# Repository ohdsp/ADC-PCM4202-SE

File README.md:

# [Open Hardware DSP Platform](http://www.ohdsp.org)
## PCM4202 ADC with single ended inputs
### Revision 1.1
###### ADC-PCM4202-SE (KiCad 4.0.2-stable)
---
# README
### Disclaimer
Copyright Paul Janicki 2016

Licensed under the TAPR Open Hardware License (www.tapr.org/OHL)

This documentation is distributed WITHOUT ANY EXPRESS OR IMPLIED WARRANTY, INCLUDING OF MERCHANTABILITY, SATISFACTORY QUALITY AND FITNESS FOR A PARTICULAR PURPOSE.

### What is this repository?

**Quick summary**

This is a single ended stereo input PCM4202 ADC. This is designed as part the Open Hardware DSP Platform.  

The PCM4202 is a hardware controlled Delta-Sigma ADC.

This repository contains the KiCad design files, manufacturing Gerber/drill files, and PDF/drawing files for this board.

### What is the project folder structure?
Starting from the top level: \
*ADC-PCM4202-SE*
+ *Bill of Materials*  - This contains the bill of materials in CVS, LibreOffice Calc and XML formats
+ *Drawings*
    + *PCB* - This contains SVG and PDF outputs of PCB copper layers and assembly drawings
    + *Schematics* - This contains the PDF schematic drawing
+ *Gerbers* - This contains the PCB Gerbers and drill drawings for manufacture, there is also a zip file ready to send to most manufacturers
+ *KiCad* - This contains the original KiCad schematic and PCB design files

### How do I get set up?

**Summary of set up**

1. Set your self up a directory on a local disk, something simple will make life easier (eg C:\Electronics on Windows as used here), but anywhere will do just fine.
2. Download the Kicad-Libs from [https://github.com/ohdsp/KiCad-Libs](https://github.com/ohdsp/KiCad-Libs) and place in C:\Electronics\Kicad-Libs (or your chosen folder) 
3. Create a OHDSP subdirectory in C:\Electronics (so C:\Electronics\OHDSP)
3. Download this project to C:\Electronics\OHDSP\ADC-PCM4202-SE
4. Fire up Kicad
5. Open the main project file C:\Electronics\OHDSP\ADC-PCM4202-SE\Schematics\ADC-PCM4202-SE.pro
6. (Optional) Setup Pcbnew component library as below.
7. Do as you wish with the project, just keep it under TAPR Open Hardware License

Make sure your git setup doesn't exclude files used in the project (like .LIB files) or things may go wrong down the line.

**KiCad Library Configuration**

Note that you need to setup a Pcbnew library, but the eeschema libraries should work without any changes if you followed the instructions above.

To setup Pcbnew libraries:

In Pcbnew go to Preferences -> Footprint Libraries Manager. Under Global Libraries tab in the top list check if there is a nickname "MyKiCadLibs-Footprints" (usually at the end of the list). If there is but it points to the wrong place then change the Library Path to point to MyKiCadLibs-Footprints (eg C:\Electronics\KiCad-Libs\MyKiCadLibs-Footprints.pretty) folder for your setup. If this is missing you can use "Append with Wizard", choose "Files on my computer", click next, browse to library location (eg C:\Electronics\KiCad-Libs\MyKiCadLibs-Footprints.pretty) and select the folder MyKiCadLibs-Footprints.pretty, click next, check the Status column states OK and the Format is KiCad (if not re-download the library) and click next, then select "To global library configuration..." and click Finish.

To setup eeschema component libraries:
Either from KiCad project window go to Tools -> Run Library Editor OR under eeschema, go to Tools -> Library Editor. Then Preferences -> Component Libraries.

The top section "Component Library Files" should ideally contain only two libraries, the "power" library that ships with KiCad and "MyKiCadLibs-Lib" available from above. To setup MyKiCadLibs-Lib as a relative path under the "User defined search path" click add. Browse to the location of KiCad-Libs you download above (eg C:\Electronics\KiCad-Libs) and click "Select Folder". Say yes to add a relative path. Under component library files click add, browse to the KiCad-libs again (eg C:\Electronics\KiCad-Libs), select file "MyKiCadLibs-Lib.lib" and click open. MyKiCadLibs-lib should appear in the component library list with no path as it will be using the user defined search path set in the box below.

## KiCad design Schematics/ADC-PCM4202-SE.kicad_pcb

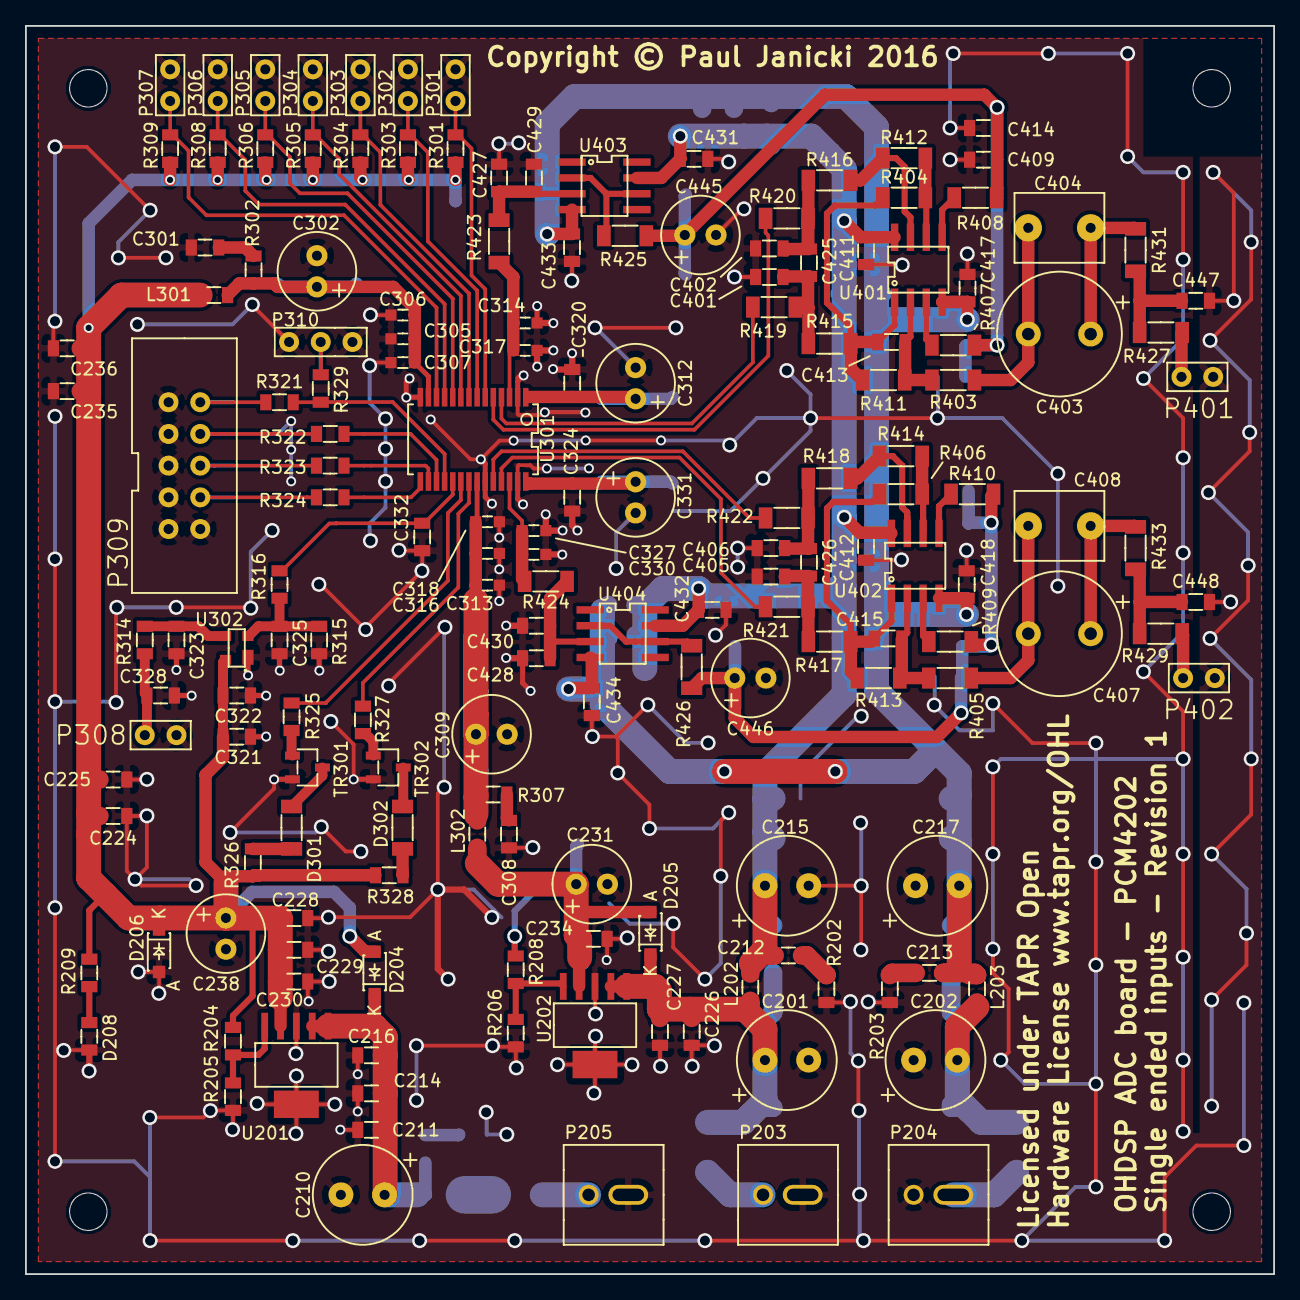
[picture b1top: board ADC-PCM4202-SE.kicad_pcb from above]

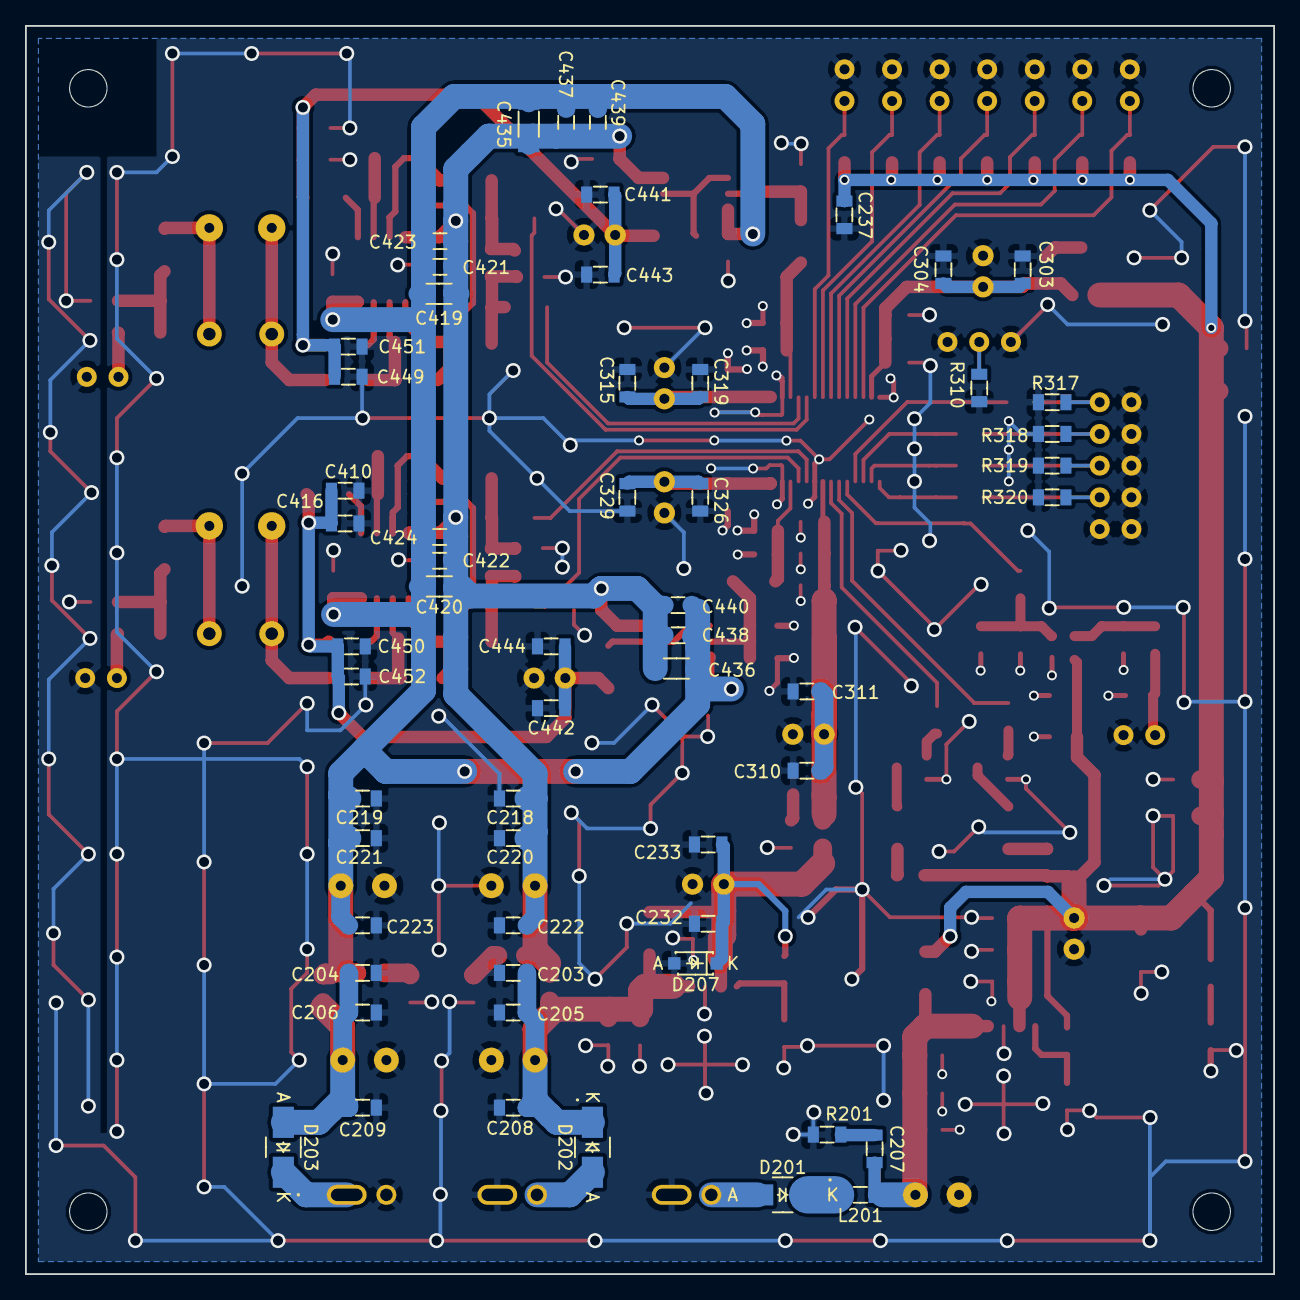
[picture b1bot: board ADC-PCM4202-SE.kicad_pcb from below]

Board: 2 copper layers, 100.0 x 100.0 mm, 228 parts (57 on the bottom side), 88 nets.

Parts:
C201, C202, C210, C215, C217: 220u; CAP-TH-D8mmP3.5mm
C203, C204, C211, C218, C219, C224, C226, C228, C232, C235, C303, C310, C315, C329: 22u; SMD-0805
C205, C206, C214, C220, C221, C225, C227, C229, C233, C236, C237, C304, C311, C319, C322, C323, C325, C326, C328, C332, C409, C410, C411, C412, C417, C418, C421, C422, C427, C428, C431, C432, C433, C434, C437, C438, C441, C442, C449, C450: 100n; SMD-0805
C207, C212, C213, C301, C308, C401, C402, C405, C406: 100p; SMD-0805
C208, C209, C216, C222, C223, C230, C234, C320, C324, C429, C430, C439, C440, C443, C444: 10n; SMD-0805
C231, C238, C302, C309, C312, C331: 220u; CAP-TH-D6.3mmP2.5mm
C305, C313: 1u; SMD-0603
C306, C314, C316, C330: 100n; SMD-0603
C307, C317, C318, C327: 10n; SMD-0603
C321: 1u; SMD-0805
C403, C407: 100u; CAP-TH-D10mmP5mm
C404, C408: 100n; CAP_TH_5mm
C413, C415, C423, C424: 1n; SMD-0805
C414, C416, C451, C452: 10u; SMD-0805
C419, C420, C435, C436: 22u; SMD-1206
C425, C426: 2n7; SMD-0805
C445, C446: 47u; CAP-TH-D6.3mmP2.5mm
C447, C448: 220p; SMD-0805
D201, D202, D203: B230A; DIODE-SMA
D204, D205, D206, D207: SBR1A40S1; DIODE-SOD-123
D208: LED; SMD-0805
D301, D302: LED; SMD-1206
L201, L202, L203, L301, L302: 600R@100MHz; SMD-0805
P201, P202, P206, P207: PIN; MountingHole_3mm
P203, P204, P205: CONN_2x1; CONN-2WAY-2.54mm-3.81mm-SPACING
P301, P302, P303, P304, P305, P306, P307, P308, P401, P402: CONN_2x1; CONN_SIL_2
P309: CONN_02X05; CONN_DIL_2X5_BOX
P310: CONN_3x1; CONN_SIL_3
R201, R202, R203, R302, R307: 47R; SMD-0805
R204, R321, R322, R323, R324, R329: 0R; SMD-0805
R205, R310, R317, R318, R319, R320: N/F; SMD-0805
R206: 2k2; SMD-0805
R208: 6k8; SMD-0805
R209, R326, R328: 470R; SMD-0805
R301, R303, R304, R305, R306, R308, R309: 10k; SMD-0805
R314, R325, R327: 1k; SMD-0805
R315: 100k; SMD-0805
R316: 100R; SMD-0805
R403, R404, R405, R406, R407, R408, R409, R410, R423, R424, R425, R426, R427, R429, R431, R433: 1k; SMD-1206
R411, R412, R413, R414: 1k5; SMD-1206
R415, R416, R417, R418: 40R2; SMD-1206
R419, R420, R421, R422: 100R; SMD-1206
TR301, TR302: TRAN-NPN-BC847; IC-SOT23
U201: TPS7A4533; IC-SOT223-6
U202: TPS7A4501; IC-SOT223-6
U301: IC-ADC-PCM4202; IC-SSOP28
U302: ADM811TART; IC-SOT143
U401, U402: OPA1642AID; IC_SOIC_8
U403, U404: OPA1641AID; IC_SOIC_8

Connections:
+9VA: C212.1, C215.1, C218.1, C220.1, C222.1, C411.1, C412.1, C419.1, C420.1, C421.1, C422.1, C423.1, C424.1, C431.1, C432.1, C435.1, C436.1, C437.1, C438.1, C439.1, C440.1, L202.2, U401.8, U402.8, U403.7, U404.7
-9VA: C213.2, C217.2, C219.2, C221.2, C223.2, C417.2, C418.2, C419.2, C420.2, C421.2, C422.2, C423.2, C424.2, C433.2, C434.2, C435.2, C436.2, C437.2, C438.2, C439.2, C440.2, L203.2, U401.4, U402.4, U403.4, U404.4
/InputFilters/ANAL+: R419.1, U301.4
/InputFilters/ANAL-: R420.1, U301.5
/InputFilters/ANAR+: R421.1, U301.25
/InputFilters/ANAR-: R422.1, U301.24
/InputFilters/VCML: C409.1, C414.1, C441.1, C443.1, C445.1, C449.1, C451.1, R407.2, R408.2, R425.1
/InputFilters/VCMR: C410.1, C416.1, C442.1, C444.1, C446.1, C450.1, C452.1, R409.2, R410.2, R426.1
/InputFilters/VCOML: C314.1, C317.1, R423.2, U301.3
/InputFilters/VCOMR: C327.1, C330.1, R424.2, U301.26
/PCM4202/ADC_RESET: C332.1, R316.1, U301.19
/PCM4202/AVCC: C309.1, C310.1, C311.1, C313.1, C316.1, C318.1, L302.2, R307.1, U301.22
/PCM4202/CLIPL: R327.1, U301.21
/PCM4202/CLIPR: R325.1, U301.20
/PCM4202/DVDD: C302.1, C303.1, C304.1, C305.1, C306.1, C307.1, L301.2, R302.1, U301.13
/PCM4202/FMT0: P301.1, R301.2, U301.6
/PCM4202/FMT1: P302.1, R303.2, U301.7
/PCM4202/FS0: P304.1, R305.2, U301.9
/PCM4202/FS1: P305.1, R306.2, U301.10
/PCM4202/FS2: P306.1, R308.2, U301.11
/PCM4202/HPFD: P307.1, R309.2, U301.12
/PCM4202/SLAVE: P303.1, R304.2, U301.8
GNDA: C201.2, C202.1, C203.2, C204.1, C205.2, C206.1, C208.2, C209.1, C210.2, C211.2, C214.2, C215.2, C216.2, C217.1, C218.2, C219.1, C220.2, C221.1, C222.2, C223.1, C224.2, C225.2, C226.2, C227.2, C228.2, C229.2, C230.2, C231.2, C232.2, C233.2, C234.2, C235.2, C236.2, C237.2, C238.2, C301.2, C302.2, C303.2, C304.2, C305.2, C306.2, C307.2, C308.2, C309.2, C310.2, C311.2, C312.2, C313.2, C314.2, C315.2, C316.2, C317.2, C318.2, C319.2, C320.2, C321.2, C322.2, C323.2, C324.2, C325.2, C326.2, C327.2, C328.2, C329.2, C330.2, C331.2, C332.2, C401.1, C402.2, C405.1, C406.2, C409.2, C410.2, C411.2, C412.2, C414.2, C416.2, C417.1, C418.1, C427.2, C428.2, C429.2, C430.2, C431.2, C432.2, C433.1, C434.1, C441.2, C442.2, C443.2, C444.2, C445.2, C446.2, C447.2, C448.2, C449.2, C450.2, C451.2, C452.2, D206.1, D207.1, D208.2, P203.2, P204.1, P205.2, P301.2, P302.2, P303.2, P304.2, P305.2, P306.2, P307.2, P308.2, P309.1, P309.3, P309.5, P309.7, P309.9, P309.10, P310.1, P310.3, P401.2, P402.2, R201.2, R202.2, R203.1, R205.1, R206.2, R310.1, R315.1, R317.1, R318.1, R319.1, R320.1, TR301.2, TR302.2, U201.3, U202.3, U301.2, U301.14, U301.23, U301.27, U302.1
unnamed: C202.2, C204.2, C206.2, C209.2, D203.1, L203.1
unnamed: C207.1, C210.1, C211.1, C214.1, C216.1, D204.2, L201.2, U201.1, U201.2
unnamed: C207.2, R201.1
unnamed: C212.2, R202.1
unnamed: C213.1, R203.2
unnamed: C301.1, R302.2
unnamed: C308.1, R307.2
unnamed: C312.1, C315.1, C319.1, C320.1, U301.1
unnamed: C323.1, R314.1, U302.3
unnamed: C324.1, C326.1, C329.1, C331.1, U301.28
unnamed: C325.1, R315.2, R316.2, U302.2
unnamed: C328.1, P308.1, R314.2
unnamed: C401.2, C425.1, R415.1, R419.2
unnamed: C402.1, C425.2, R416.1, R420.2
unnamed: C403.1, C404.1, R431.1
unnamed: C403.2, C404.2, R403.2
unnamed: C405.2, C426.1, R417.1, R421.2
unnamed: C406.1, C426.2, R418.1, R422.2
unnamed: C407.1, C408.1, R433.1
unnamed: C407.2, C408.2, R405.2
unnamed: C413.1, R403.1, R411.2, U401.2
unnamed: C413.2, R404.1, R411.1, R415.2, U401.1
unnamed: C415.1, R405.1, R413.2, U402.2
unnamed: C415.2, R406.1, R413.1, R417.2, U402.1
unnamed: C427.1, C429.1, R423.1, U403.3
unnamed: C428.1, C430.1, R424.1, U404.3
unnamed: C447.1, R427.1, R431.2
unnamed: C448.1, R429.1, R433.2
unnamed: D201.1, P205.1
unnamed: D201.2, L201.1
unnamed: D202.1, P203.1
unnamed: D203.2, P204.2
unnamed: D208.1, R209.1
unnamed: D301.1, R326.1
unnamed: D301.2, TR301.3
unnamed: D302.1, R328.1
unnamed: D302.2, TR302.3
unnamed: P309.2, R317.2, R321.1
unnamed: P309.4, R318.2, R322.1
unnamed: P309.6, R319.2, R323.1
unnamed: P309.8, R320.2, R324.1
unnamed: P310.2, R310.2, R329.1
unnamed: P401.1, R427.2
unnamed: P402.1, R429.2
unnamed: R204.2, R205.2, U201.5
unnamed: R206.1, R208.2, U202.5
unnamed: R321.2, R329.2, U301.18
unnamed: R322.2, U301.17
unnamed: R323.2, U301.16
unnamed: R324.2, U301.15
unnamed: R325.2, TR301.1
unnamed: R327.2, TR302.1
unnamed: R404.2, R412.2, U401.6
unnamed: R406.2, R414.2, U402.6
unnamed: R407.1, U401.3
unnamed: R408.1, U401.5
unnamed: R409.1, U402.3
unnamed: R410.1, U402.5
unnamed: R412.1, R416.2, U401.7
unnamed: R414.1, R418.2, U402.7
unnamed: R425.2, U403.2, U403.6
unnamed: R426.2, U404.2, U404.6
VAA: C231.1, C232.1, C233.1, C234.1, D205.1, D207.2, L302.1, R208.1, U202.4
VCC: C201.1, C203.1, C205.1, C208.1, C226.1, C227.1, D202.2, D205.2, L202.1, U202.1, U202.2
VDD: C224.1, C225.1, C228.1, C229.1, C230.1, C235.1, C236.1, C237.1, C238.1, C321.1, C322.1, D204.1, D206.2, L301.1, R204.1, R209.2, R301.1, R303.1, R304.1, R305.1, R306.1, R308.1, R309.1, R326.2, R328.2, U201.4, U302.4

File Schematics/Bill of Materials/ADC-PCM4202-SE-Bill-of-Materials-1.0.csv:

,"ADC-PCM4202-SE Bill of Materials Release 1.0",,,,,
,"24/01/16",,,,,
"Id","Designator","Package","Quantity","Designation","Detail",
"1","C413,C415,C423,C424","SMD-0805","4","1n","50V NP0 5%",
"2","R411,R412,R413,R414","SMD-1206","4","1k5","MELF 0204",
"3","R429,R427,R403,R404,R405,R406,R407,R408,R409,R410,R423,R424,R425,R426,R431,R433","SMD-1206","16","1k","MELF 0204",
"4","P201,P202,P206,P207","MountingHole_3mm","4","PIN","Mounting hole only",
"5","C201,C202,C210,C215,C217","CAP-TH-D8mmP3.5mm","5","220u","'=>35V eg Panasonic EEU-FC1V221L",
"6","C203,C204,C211,C218,C219,C226,C228,C232,C303,C310,C315,C329,C224,C235","SMD-0805","14","22u","35V X5R 20%",
"7","C205,C206,C214,C220,C221,C227,C229,C233,C304,C311,C319,C322,C323,C325,C326,C328,C332,C411,C412,C417,C418,C421,C422,C427,C428,C431,C432,C433,C434,C437,C438,C441,C442,C225,C236,C237,C409,C410,C449,C450","SMD-0805","40","100n","50V X7R 10%",
"8","C207,C212,C213,C301,C308,C401,C402,C405,C406","SMD-0805","9","100p","50V NP0 5%",
"9","C208,C209,C216,C222,C223,C230,C234,C320,C324,C429,C430,C439,C440,C443,C444","SMD-0805","15","10n","50V X7R 10%",
"10","C231,C302,C309,C312,C331,C238","CAP-TH-D6.3mmP2.5mm","6","220u","'=>16V eg Panasonic EEU-FR1C221",
"11","C305,C313","SMD-0603","2","1u","16V X7R 10%",
"12","C306,C316,C314,C330","SMD-0603","4","100n","50V X7R 10%",
"13","C307,C318,C317,C327","SMD-0603","4","10n","50V X7R 10%",
"14","C321","SMD-0805","1","1u","25V X7R 10%",
"15","C403,C407","CAP-TH-D10mmP5mm","2","100u","'=>50V Panasonic EEUFC1H101 - In audio path",
"16","C404,C408","CAP_TH_5mm","2","100n","63V 5mm Film Capacitor",
"17","C419,C420,C435,C436","SMD-1206","4","22u","35V X5R 20%",
"18","C425,C426","SMD-0805","2","2n7","50V NP0 5%",
"19","D201,D202,D203","DIODE-SMA","3","B230A","Diodes Inc. B230A-13-F",
"20","D204,D205,D206,D207","DIODE-SOD-123","4","SBR1A40S1","Diodes Inc. SBR1A40S1",
"21","D301,D302","SMD-1206","2","LED","Green or Red 1206 LED eg Avago HSMG-C150 (or 0805 parts may fit)",
"22","L201,L202,L203,L301,L302","SMD-0805","5","600R@100MHz","'=>1A eg Wruth 742792040, TDK MPZ2012S601A",
"23","P203,P204,P205","CONN-2WAY-2.54mm-3.81mm-SPACING","3","CONN_2x1","Any 2.54mm  or 3.81mm screw terminal eg CamdenBoss CTB0308/2",
"24","P301,P302,P303,P304,P305,P306,P307,P308,P401,P402","CONN_SIL_2","10","CONN_2x1","P301-P307 are 2.54mm pitch pin header (jumpers), the rest can wire directly",
"25","P309","CONN_DIL_2X5_BOX","1","CONN_02X05","2x5 2.54mm box header",
"26","R201,R202,R203,R302,R307","SMD-0805","5","47R","100mW",
"27","R204,R321,R322,R323,R324,R329","SMD-0805","6","0R","100mW",
"28","R205,R317,R318,R319,R320,R310","SMD-0805","6","N/F","NOT FITTED",
"29","R206","SMD-0805","1","2k2","100mW",
"30","R208","SMD-0805","1","6k8","100mW",
"31","R301,R303,R304,R305,R306,R308,R309","SMD-0805","7","10k","100mW",
"32","R314,R325,R327","SMD-0805","3","1k","100mW",
"33","R315","SMD-0805","1","100k","100mW",
"34","R316","SMD-0805","1","100R","100mW",
"35","R326,R328,R209","SMD-0805","3","470R","100mW",
"36","R415,R416,R417,R418","SMD-1206","4","40R2","MELF 0204",
"37","R419,R420,R421,R422","SMD-1206","4","100R","MELF 0204",
"38","TR301,TR302","IC-SOT23","2","TRAN-NPN-BC847","BC847B SOT-23",
"39","U201","IC-SOT223-6","1","TPS7A4533","Texas Instruments TPS7A4533DCQT low noise regulator",
"40","U202","IC-SOT223-6","1","TPS7A4501","Texas Instruments TPS7A4501DCQT low noise regulator",
"41","U302","IC-SOT143","1","ADM811TART","Analog Devices ADM811TART",
"42","U403,U404","IC_SOIC_8","2","OPA1641AID","Texas Instruments OPA1641AID or low noise JFET single op-amp",
"43","U301","IC-SSOP28","1","IC-ADC-PCM4202","Texas Instruments PCM4202DBT",
"44","U401,U402","IC_SOIC_8","2","OPA1642AID","Texas Instruments OPA1642AID or other dual op-amp",
"45","C445,C446","CAP-TH-D6.3mmP2.5mm","2","47u","'=>16V eg Panasonic EEUFR1H470",
"46","C448,C447","SMD-0805","2","220p","50V NP0 5%",
"47","P310","CONN_SIL_3","1","CONN_3x1","2.54mm pitch pin header or wire directly",
"48","D208","SMD-0805","1","LED","Green or Red 0805 LED eg Avago HSMC-C170",
"49","C414,C416,C451,C452","SMD-0805","4","10u","25V X7R 10%",

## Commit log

2016-01-24 Release 1.0
    Release 1.0
2016-04-23 Revision 1.1

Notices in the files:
Schematics/ADC-PCM4202-SE.kicad_pcb:
Copyright © Paul Janicki 2016
Licensed under TAPR Open
